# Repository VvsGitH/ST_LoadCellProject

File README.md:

# **Load Cell Project**
> Student's project at Politecnico di Bari  
> *Authors:  
> &nbsp;&nbsp;&nbsp; Gentile Roberto  
> &nbsp;&nbsp;&nbsp; Lotano Daniel  
> &nbsp;&nbsp;&nbsp; Paparella Santorsola Vito  
> Teacher:  
> &nbsp;&nbsp;&nbsp; Adamo Francesco*

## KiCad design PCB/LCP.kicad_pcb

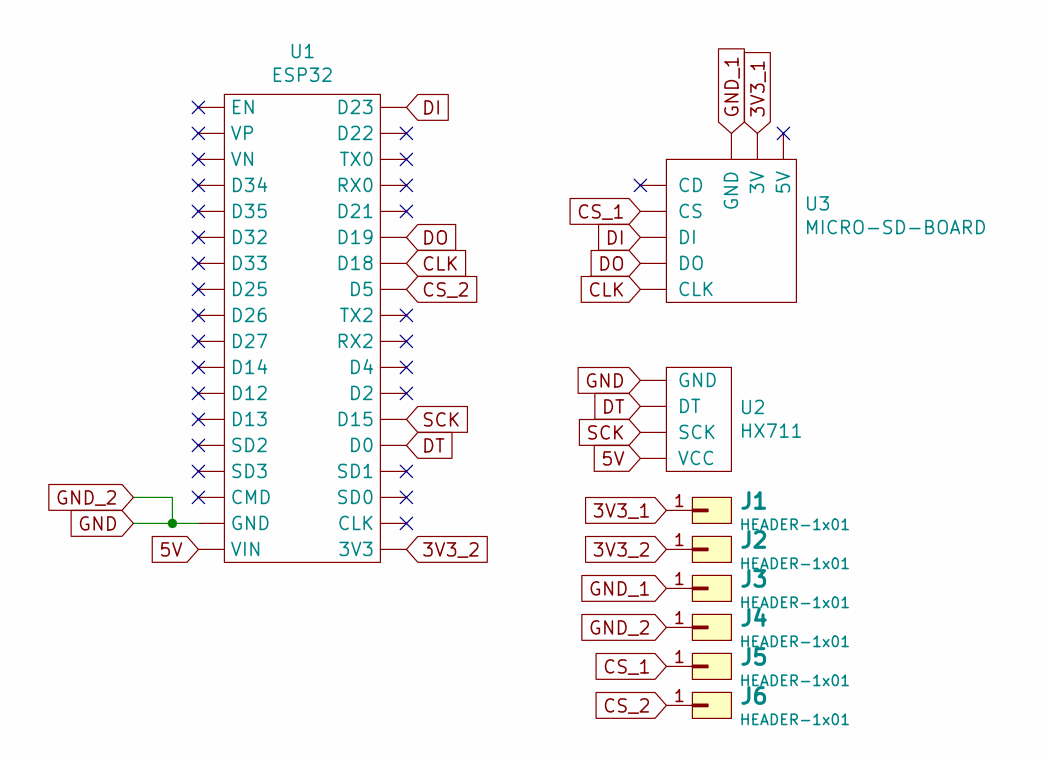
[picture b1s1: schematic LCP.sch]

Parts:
J1, J2, J3, J4, J5, J6: HEADER-1x01; PAD
U1: ESP32; ESP32-DEVKIT-V1
U2: HX711
U3: MICRO-SD-BOARD

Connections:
3V3_1: J1.1, U3.7 (3V)
3V3_2: J2.1, U1.19 (3V3)
5V: U1.18 (VIN), U2.4 (VCC)
CLK: U1.30 (D18), U3.5 (CLK)
CS_1: J5.1, U3.2 (CS)
CS_2: J6.1, U1.29 (D5)
DI: U1.36 (D23), U3.3 (DI)
DO: U1.31 (D19), U3.4 (DO)
DT: U1.23 (D0), U2.2 (DT)
GND: J4.1, U1.17 (GND), U2.1 (GND)
GND_1: J3.1, U3.6 (GND)
SCK: U1.24 (D15), U2.3 (SCK)

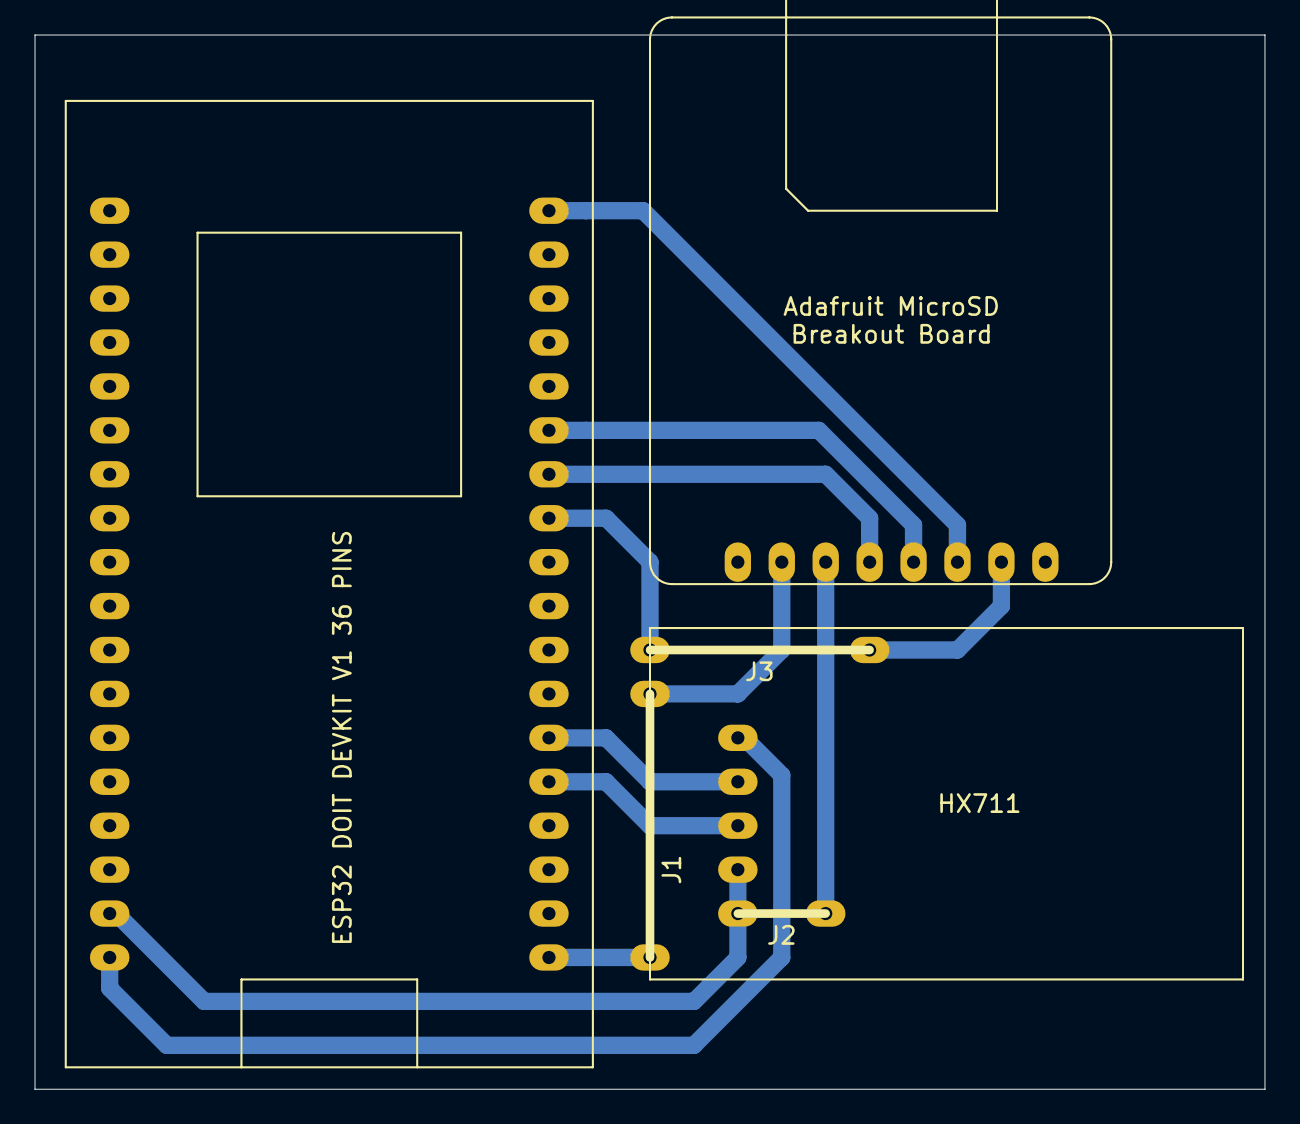
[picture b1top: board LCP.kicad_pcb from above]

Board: 2 copper layers, 71.1 x 61.0 mm, 9 parts (0 on the bottom side), 12 nets.

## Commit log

2020-04-15 Backup commit with Git
